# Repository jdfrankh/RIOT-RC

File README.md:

### RIOT-RC
This library contains hardware and software files for Robo RIOT's Rc controllers. These sets are meant to control 1lb, 3lb, and possibly 5lb robotics in a compact package, allowing any individual to easily create their own open-source battle bot electronics set.  

## Quickstart -- Preassembled Remote and Receiver

The RIOT RC has the following basic specs

# Receiver
| Parameter | Value |
|----------|----------|
| Supply Voltage  | 5V - 36V  |
| Idle Amperage Time  | .05A  |
| Default ESC Hookups | 2 |
| Default Servo Hookups | 2 |
| DC Drives | 2 |

# Remote 
| Parameter | Value |
|----------|----------|
| Operating Time | ~3 hours  |
| Radio Range  | ~40-60m  |
| Analog Joysticks | 2 |
| Buttons | 4 |

# Hookup

The pinout of the Receiver is the following:

Attach your receiver as according to the diagram:

# Basic Operation

The staring operation of the remote goes as such.

1. Start your remote
2. Select your desired reciever by username
3. Control your reciever

The controls for selecting your receiver go as such:

The OLED screen will display all **Powered** receivers automatically with their assigned name. Select one to automatically connect it. 

The controls for the remote after the reciver go as such: 

Keep in mind that there is a **Software** based arming mechanism for the BLDC motor. The receiver will not activate it unless the arming command is first sent. It may take about 5 seconds to arm your receiver. **Please be cautious when actiavate the BLDC, as it's speed rating may be enough to harm.**

The brushed motors are programmed to act as a drive, moving according to a two wheeled battlebot. Although the supply voltage is attached to the motor drive, the original code is deisgned around a 6V N20, and thus creates a PWM signal to prevent users from frying the motor. To change this. Please refer to the **Change code** section for more information.

## Simple edits - Uploading Sketches

Many values as of right now are hard-coded into the remote or receiver to change, and most of those changes can be altered by re-flashing them. The software was created in PlatoformIO, and integrated IDE into VSCode for microcontrollers. Many resources are avaliable for you to download and operate the software.

Once PlatformIO has been downloaded, clone the repository and naviage to /RIOT-RC/PlatformIO Imports/ and select the platoformIO directory. 

**Caution**: The receiver is attached to the battery voltage. **FOR THE RECEIVER DO NOT ATTACH A USB WHILE A LIPO BATTERY IS ATTACHED. YOU WILL FRY YOUR USB PORT AND YOUR COMPUTER**

Most easily accessible commands will be placed at the top of main.cpp for ease of access. Alterations from the basic control scheme will be implemented later. 

# Battery Charging

The Remote has a one cell battery charger. Simply attach the charger to your USB to recharge it.

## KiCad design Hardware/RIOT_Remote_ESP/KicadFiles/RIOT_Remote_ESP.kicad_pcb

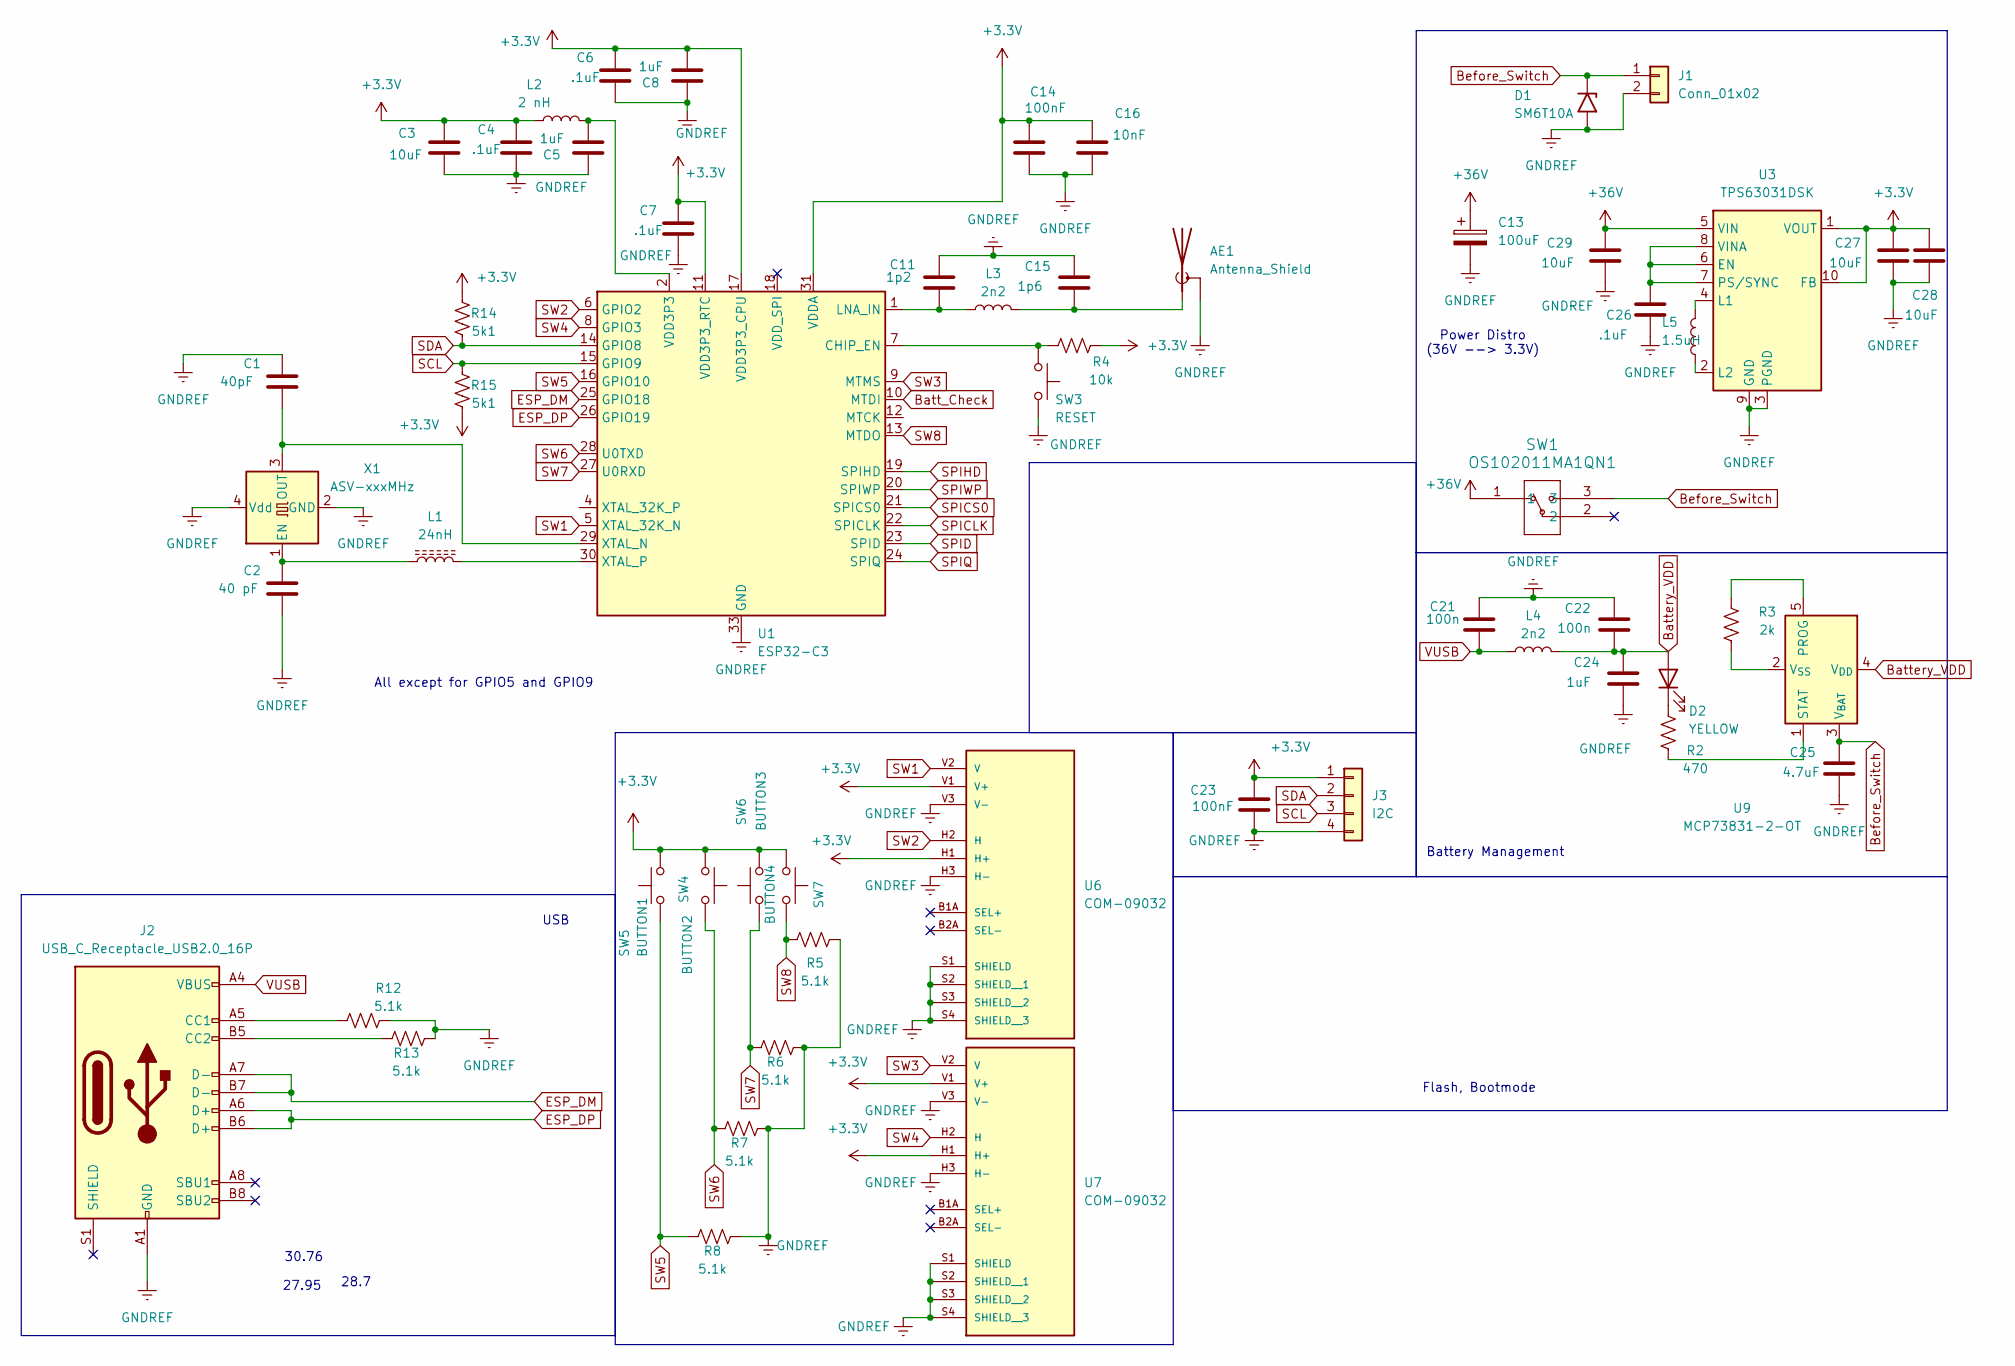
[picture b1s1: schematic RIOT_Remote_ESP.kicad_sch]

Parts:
AE1: Antenna_Shield; U.FL_Molex_MCRF_73412-0110_Vertical
C1: 40pF; C_0402_1005Metric_Pad0.74x0.62mm_HandSolder
C2: 40 pF; C_0402_1005Metric_Pad0.74x0.62mm_HandSolder
C3: 10uF; C_1206_3216Metric_Pad1.33x1.80mm_HandSolder
C4, C6, C7, C26: .1uF; C_0402_1005Metric_Pad0.74x0.62mm_HandSolder
C5, C8, C24: 1uF; C_0402_1005Metric_Pad0.74x0.62mm_HandSolder
C11: 1p2; C_0402_1005Metric_Pad0.74x0.62mm_HandSolder
C13: 100uF; CP_Elec_4x5.4
C14, C23: 100nF; C_0402_1005Metric_Pad0.74x0.62mm_HandSolder
C15: 1p6; C_0402_1005Metric_Pad0.74x0.62mm_HandSolder
C16: 10nF; C_0402_1005Metric_Pad0.74x0.62mm_HandSolder
C21, C22: 100n; C_0402_1005Metric_Pad0.74x0.62mm_HandSolder
C25: 4.7uF; C_0402_1005Metric_Pad0.74x0.62mm_HandSolder
C27, C28, C29: 10uF; C_0603_1608Metric_Pad1.08x0.95mm_HandSolder
D1: SM6T10A; D_SMB
D2: YELLOW; LED_1206_3216Metric_Pad1.42x1.75mm_HandSolder
J1: Conn_01x02; PinSocket_1x02_P2.54mm_Vertical
J2: USB_C_Receptacle_USB2.0_16P; USB_C_Receptacle_GCT_USB4085
J3: I2C; PinHeader_1x04_P2.54mm_Vertical
L1: 24nH; L_0603_1608Metric_Pad1.05x0.95mm_HandSolder
L2: 2 nH; L_0603_1608Metric_Pad1.05x0.95mm_HandSolder
L3, L4: 2n2; L_0603_1608Metric_Pad1.05x0.95mm_HandSolder
L5: 1.5uH; L_Coilcraft_LPS3010
R2: 470; R_0402_1005Metric_Pad0.72x0.64mm_HandSolder
R3: 2k; R_0402_1005Metric_Pad0.72x0.64mm_HandSolder
R4: 10k; R_0402_1005Metric_Pad0.72x0.64mm_HandSolder
R5, R6, R7, R8, R12, R13: 5.1k; R_0402_1005Metric_Pad0.72x0.64mm_HandSolder
R14, R15: 5k1; R_0402_1005Metric_Pad0.72x0.64mm_HandSolder
SW1: OS102011MA1QN1; OS102011MA1QN1_CNK
SW3: RESET; SW_PUSH_6mm_H4.3mm
SW4: BUTTON2; SW_Tactile_SPST_Angled_PTS645Vx58-2LFS
SW5: BUTTON1; SW_PUSH_6mm_H4.3mm
SW6: BUTTON3; SW_PUSH_6mm_H4.3mm
SW7: BUTTON4; SW_Tactile_SPST_Angled_PTS645Vx58-2LFS
U1: ESP32-C3; QFN-32-1EP_5x5mm_P0.5mm_EP3.7x3.7mm
U3: TPS63031DSK; WSON-10-1EP_2.5x2.5mm_P0.5mm_EP1.2x2mm
U6, U7: COM-09032; XDCR_COM-09032; PARTREV N/A
U9: MCP73831-2-OT; SOT-23-5
X1: ASV-xxxMHz; Oscillator_SMD_Abracon_ASE-4Pin_3.2x2.5mm_HandSoldering

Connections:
+3.3V: C3.1, C4.1, C6.1, C7.1, C8.2, C14.1, C16.1, C23.1, C27.1, C28.1, J3.1, L2.1, R4.2, R14.2, R15.1, SW4.1, SW5.2, SW6.2, SW7.1, U1.11 (VDD3P3_RTC), U1.17 (VDD3P3_CPU), U1.31 (VDDA), U1.32 (VDDA), U3.1 (VOUT), U3.10 (FB), U6.H1 (H+), U6.V1 (V+), U7.H1 (H+), U7.V1 (V+)
+36V: C13.1, C29.1, SW1.1, U3.5 (VIN); also elsewhere on the board
Batt_Check: U1.10 (MTDI)
Battery_VDD: C22.2, C24.1, D2.2 (A), L4.2, U9.4 (V_{DD})
Before_Switch: C25.1, D1.1 (A1), J1.1, SW1.3, U9.3 (V_{BAT}); also elsewhere on the board
ESP_DM: J2.A7 (D-), J2.B7 (D-), U1.25 (GPIO18)
ESP_DP: J2.A6 (D+), J2.B6 (D+), U1.26 (GPIO19)
GNDREF: AE1.2 (Shield), C1.1, C2.2, C3.2, C4.2, C5.1, C6.2, C7.2, C8.1, C11.1, C13.2, C14.2, C15.1, C16.2, C21.1, C22.1, C23.2, C24.2, C25.2, C26.2, C27.2, C28.2, C29.2, D1.2 (A2), J1.2, J2.A1 (GND), J2.A12 (GND), J2.B1 (GND), J2.B12 (GND), J3.4, R5.2, R6.2, R7.2, R8.2, R12.2, R13.2, SW3.2, U1.33 (GND), U3.3 (PGND), U3.9 (GND), U3.11 (PGND), U6.H3 (H-), U6.S1 (SHIELD), U6.S2 (SHIELD__1), U6.S3 (SHIELD__2), U6.S4 (SHIELD__3), U6.V3 (V-), U7.H3 (H-), U7.S1 (SHIELD), U7.S2 (SHIELD__1), U7.S3 (SHIELD__2), U7.S4 (SHIELD__3), U7.V3 (V-), X1.2 (GND), X1.4 (Vdd); also elsewhere on the board
unnamed: AE1.1 (A), C15.2, L3.2
unnamed: C5.2, L2.2, U1.2 (VDD3P3), U1.3 (VDD3P3)
unnamed: D2.1 (K), R2.2
unnamed: J2.A5 (CC1), R12.1
unnamed: J2.B5 (CC2), R13.1
unnamed: R4.1, SW3.1, U1.7 (CHIP_EN)
unnamed: C11.2, L3.1, U1.1 (LNA_IN)
unnamed: C1.2, U1.29 (XTAL_N), X1.3 (OUT)
unnamed: L1.2, U1.30 (XTAL_P)
unnamed: C26.1, U3.6 (EN), U3.7 (PS/SYNC), U3.8 (VINA)
unnamed: L5.2, U3.4 (L1)
unnamed: L5.1, U3.2 (L2)
unnamed: R3.2, U9.5 (PROG)
unnamed: R2.1, U9.1 (STAT)
unnamed: R3.1, U9.2 (V_{SS})
unnamed: C2.1, L1.1, X1.1 (EN)
SCL: J3.3, R15.2, U1.15 (GPIO9)
SDA: J3.2, R14.1, U1.14 (GPIO8)
SPICLK: U1.22 (SPICLK)
SPICS0: U1.21 (SPICS0)
SPID: U1.23 (SPID)
SPIHD: U1.19 (SPIHD)
SPIQ: U1.24 (SPIQ)
SPIWP: U1.20 (SPIWP)
SW1: U1.5 (XTAL_32K_N), U6.V2 (V)
SW2: U1.6 (GPIO2), U6.H2 (H)
SW3: U1.9 (MTMS), U7.V2 (V)
SW4: U1.8 (GPIO3), U7.H2 (H)
SW5: R8.1, SW5.1, U1.16 (GPIO10)
SW6: R7.1, SW4.2, U1.28 (U0TXD)
SW7: R6.1, SW6.1, U1.27 (U0RXD)
SW8: R5.1, SW7.2, U1.13 (MTDO)
VUSB: C21.2, J2.A4 (VBUS), J2.A9 (VBUS), J2.B4 (VBUS), J2.B9 (VBUS), L4.1

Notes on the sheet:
28.7
Battery Management
Power Distro (36V --> 3.3V)
Flash, Bootmode
27.95
All except for GPIO5 and GPIO9
USB
30.76

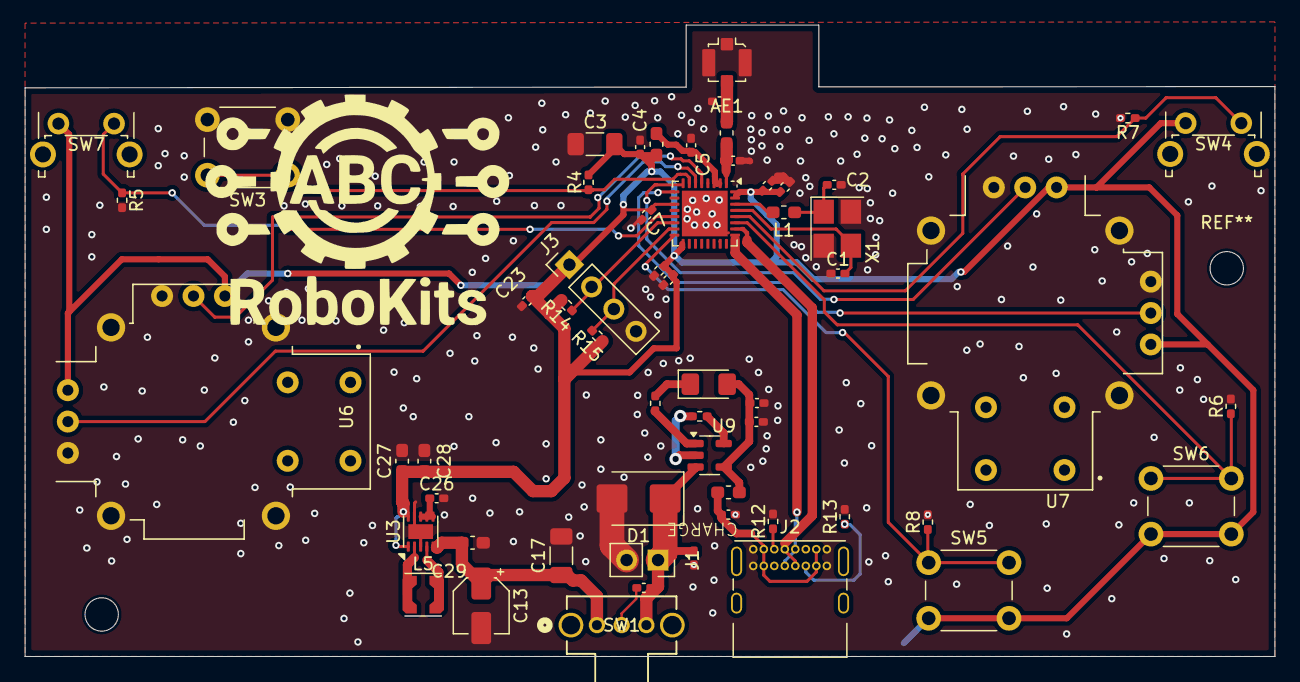
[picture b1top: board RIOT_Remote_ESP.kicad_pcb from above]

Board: 2 copper layers, 101.1 x 51.1 mm, 58 parts (0 on the bottom side), 34 nets.

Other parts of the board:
C17: 1 uF; C_1206_3216Metric_Pad1.33x1.80mm_HandSolder
C25#2: 4.7uF; C_0402_1005Metric_Pad0.74x0.62mm_HandSolder

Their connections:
+36V: C17.1; also elsewhere on the board
Before_Switch: C25#2.1; also elsewhere on the board
GNDREF: C17.2, C25#2.2; also elsewhere on the board

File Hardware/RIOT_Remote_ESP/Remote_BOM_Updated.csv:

Value,Reference,Footprint,Digikey Link to Item,Qty
MCP73831-2-OT,U9,Package_TO_SOT_SMD:SOT-23-5,https://www.digikey.com/en/products/filter/battery-chargers/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,1
ASV-40MHz,X1,Oscillator:Oscillator_SMD_Abracon_ASE-4Pin_3.2x2.5mm_HandSoldering,https://www.digikey.com/en/products/detail/kyocera-avx/CX322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,1
TPS63031DSK,U3,Package_SON:WSON-10-1EP_2.5x2.5mm_P0.5mm_EP1.2x2mm,https://www.digikey.com/en/products/detail/texas-instruments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,1
ESP32-C3FH,U1,Package_DFN_QFN:QFN-32-1EP_5x5mm_P0.5mm_EP3.7x3.7mm,https://www.digikey.com/en/products/detail/espressif-systems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,1
SM6T10A,D1,Diode_SMD:D_SMB,https://www.digikey.com/en/products/detail/stmicroelectronic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,1
USB_C_Receptacle_USB2.0_16P,J2,Connector_USB:USB_C_Receptacle_GCT_USB4085,https://www.digikey.com/en/products/detail/gct/USB4085-GF-A/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,1
Antenna_Shield,AE1,Connector_Coaxial:U.FL_Molex_MCRF_73412-0110_Vertical,https://www.digikey.com/en/products/detail/hirose-electric-c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,1
12pF,"C1,C2",Capacitor_SMD:C_0402_1005Metric_Pad0.74x0.62mm_HandSolder,,2
10uF,"C3,C27,C28,C29","Capacitor_SMD:C_0603_1608Metric_Pad1.08x0.95mm_HandSolder,Capacitor_SMD:C_1206_3216Metric_Pad1.33x1.80mm_HandSolder",,4
1uF,"C5,C8,C24",Capacitor_SMD:C_0402_1005Metric_Pad0.74x0.62mm_HandSolder,,3
1p2,C11,Capacitor_SMD:C_0402_1005Metric_Pad0.74x0.62mm_HandSolder,,1
100uF,C13,Capacitor_SMD:CP_Elec_4x5.4,,1
100nF,"C14,C23,C21,C22,C4,C6,C7,C26",Capacitor_SMD:C_0402_1005Metric_Pad0.74x0.62mm_HandSolder,,8
1p6,C15,Capacitor_SMD:C_0402_1005Metric_Pad0.74x0.62mm_HandSolder,,1
10nF,C16,Capacitor_SMD:C_0402_1005Metric_Pad0.74x0.62mm_HandSolder,,1
4.7uF,C25,Capacitor_SMD:C_0402_1005Metric_Pad0.74x0.62mm_HandSolder,,1
YELLOW,D2,LED_SMD:LED_1206_3216Metric_Pad1.42x1.75mm_HandSolder,,1
24nH,L1,Inductor_SMD:L_0603_1608Metric_Pad1.05x0.95mm_HandSolder,,1
2 nH,L2,Inductor_SMD:L_0603_1608Metric_Pad1.05x0.95mm_HandSolder,,1
2n2,"L3,L4",Inductor_SMD:L_0603_1608Metric_Pad1.05x0.95mm_HandSolder,,2
1.5uH,L5,Inductor_SMD:L_Coilcraft_LPS3010,,1
470,R2,Resistor_SMD:R_0402_1005Metric_Pad0.72x0.64mm_HandSolder,,1
2k,R3,Resistor_SMD:R_0402_1005Metric_Pad0.72x0.64mm_HandSolder,,1
10k,R4,Resistor_SMD:R_0402_1005Metric_Pad0.72x0.64mm_HandSolder,,1
5.1k,"R14,R15,R5,R6,R7,R8,R12,R13",Resistor_SMD:R_0402_1005Metric_Pad0.72x0.64mm_HandSolder,,8

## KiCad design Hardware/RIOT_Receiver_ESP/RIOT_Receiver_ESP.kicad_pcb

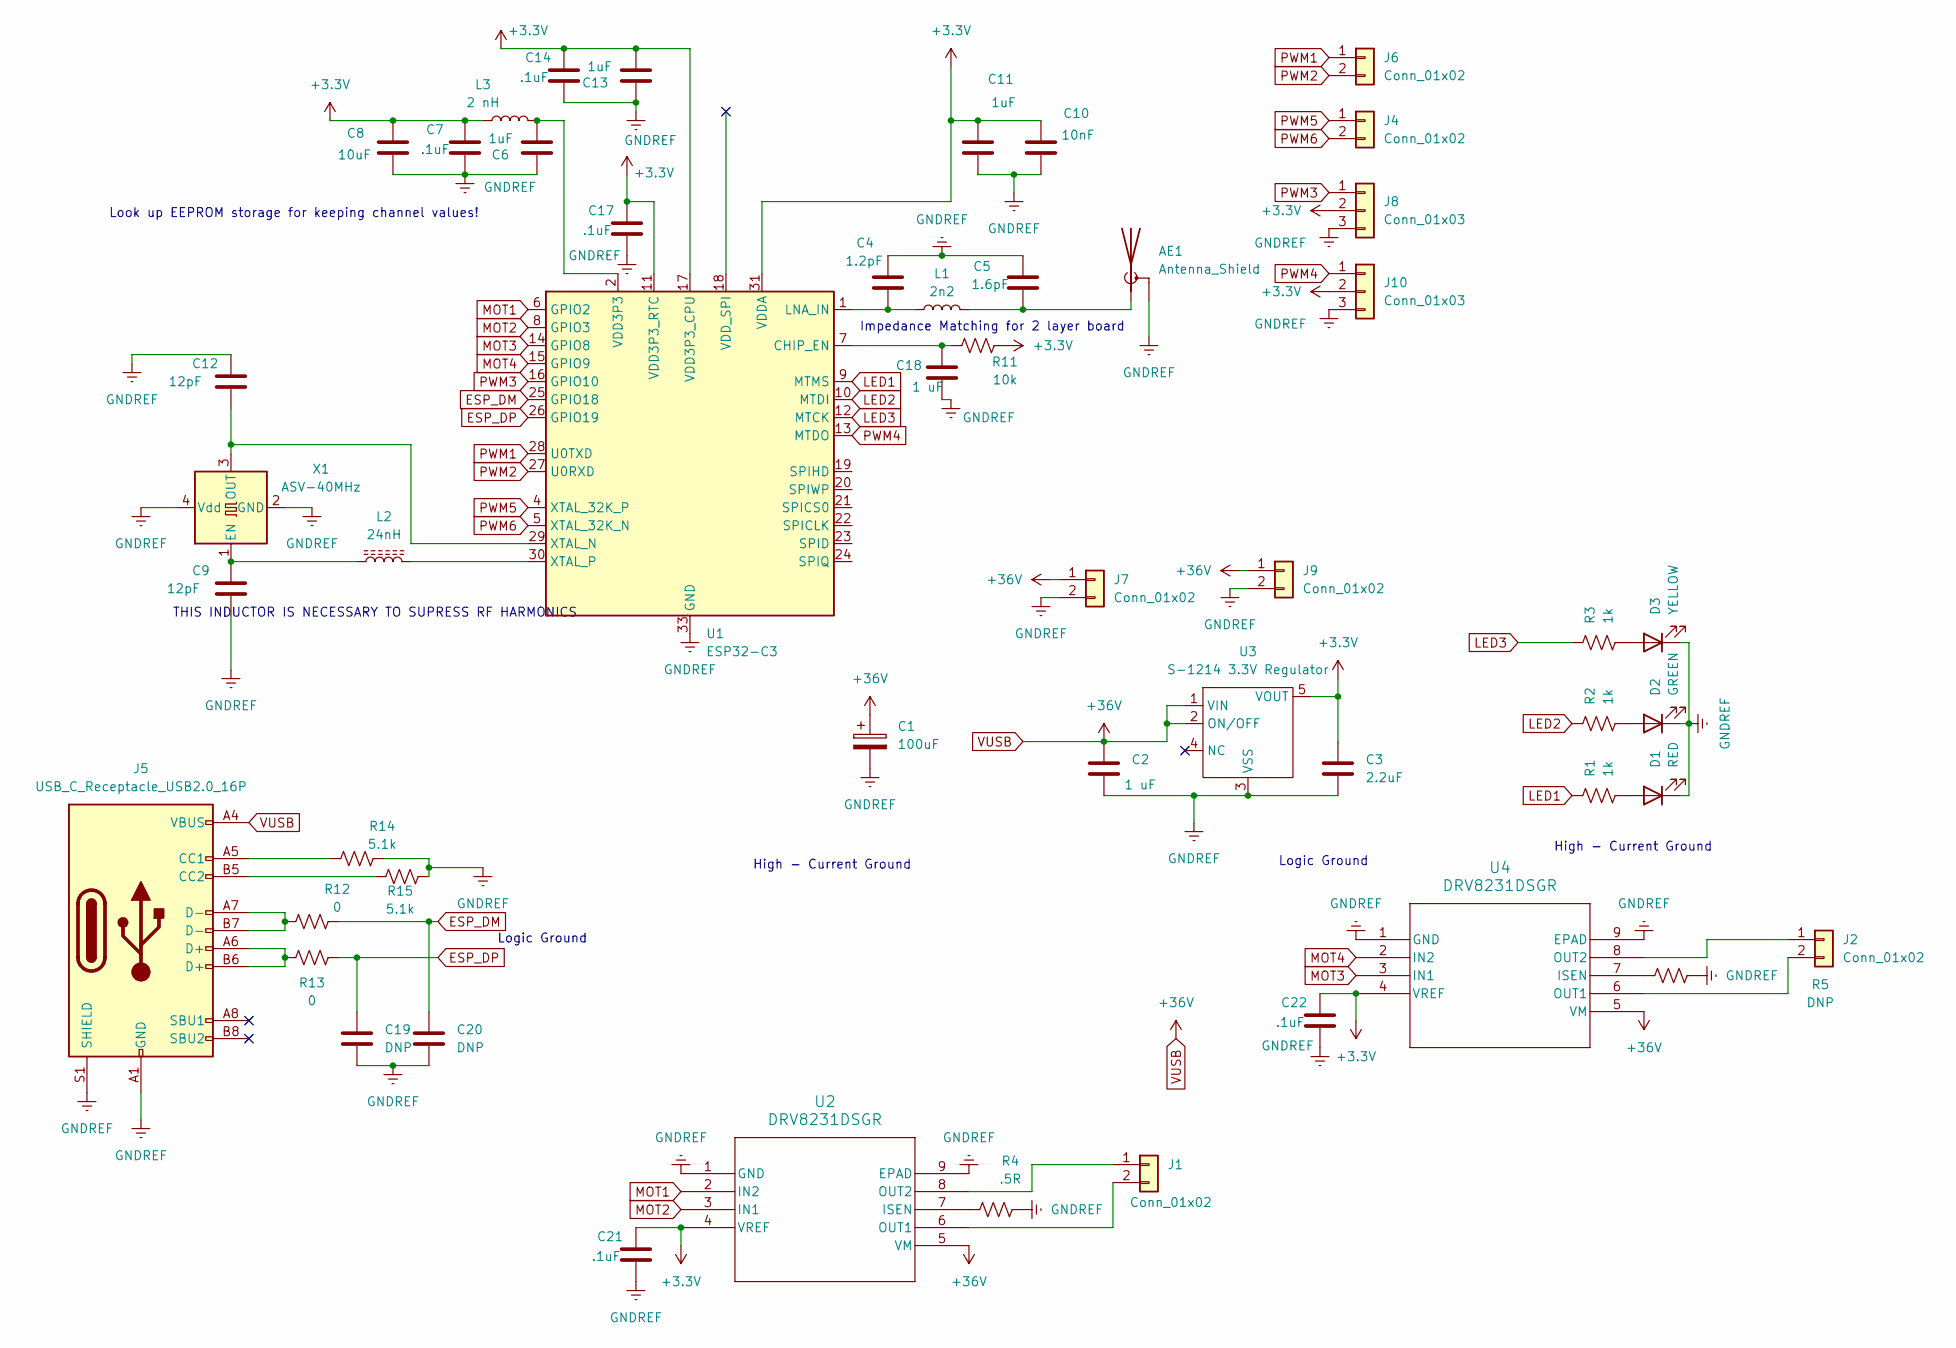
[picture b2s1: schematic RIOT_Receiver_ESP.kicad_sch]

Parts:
AE1: Antenna_Shield
C1: 100uF; C_Elec_8x10.2
C2, C18: 1 uF; C_0402_1005Metric_Pad0.74x0.62mm_HandSolder
C3: 2.2uF; C_0603_1608Metric_Pad1.08x0.95mm_HandSolder
C4: 1.2pF; C_0402_1005Metric_Pad0.74x0.62mm_HandSolder
C5: 1.6pF; C_0402_1005Metric_Pad0.74x0.62mm_HandSolder
C6, C11, C13: 1uF; C_0402_1005Metric_Pad0.74x0.62mm_HandSolder
C7, C14, C17, C21, C22: .1uF; C_0402_1005Metric_Pad0.74x0.62mm_HandSolder
C8: 10uF; C_0402_1005Metric_Pad0.74x0.62mm_HandSolder
C9, C12: 12pF; C_0402_1005Metric_Pad0.74x0.62mm_HandSolder
C10: 10nF; C_0402_1005Metric_Pad0.74x0.62mm_HandSolder
C19, C20: DNP; C_0402_1005Metric_Pad0.74x0.62mm_HandSolder
D1: RED; LED_1206_3216Metric_Pad1.42x1.75mm_HandSolder
D2: GREEN; LED_1206_3216Metric_Pad1.42x1.75mm_HandSolder
D3: YELLOW; LED_1206_3216Metric_Pad1.42x1.75mm_HandSolder
J1, J2, J4, J6, J7, J9: Conn_01x02; PinHeader_1x02_P2.54mm_Vertical
J5: USB_C_Receptacle_USB2.0_16P; USB_C_Receptacle_GCT_USB4085
J8, J10: Conn_01x03; PinHeader_1x03_P2.54mm_Vertical
L1: 2n2; L_0603_1608Metric_Pad1.05x0.95mm_HandSolder
L2: 24nH; L_0603_1608Metric_Pad1.05x0.95mm_HandSolder
L3: 2 nH; L_0603_1608Metric_Pad1.05x0.95mm_HandSolder
R1, R2, R3: 1k; R_0402_1005Metric_Pad0.72x0.64mm_HandSolder
R4: .5R; L_1206_3216Metric_Pad1.22x1.90mm_HandSolder
R5: DNP; L_1206_3216Metric_Pad1.22x1.90mm_HandSolder
R11: 10k; R_0402_1005Metric_Pad0.72x0.64mm_HandSolder
R12, R13: 0; R_0402_1005Metric_Pad0.72x0.64mm_HandSolder
R14, R15: 5.1k; R_0402_1005Metric_Pad0.72x0.64mm_HandSolder
U1: ESP32-C3; QFN-32-1EP_5x5mm_P0.5mm_EP3.7x3.7mm
U2, U4: DRV8231DSGR; WSON8_DRV8231_TEX
U3: S-1214 3.3V Regulator; TO-252-5_TabPin3
X1: ASV-40MHz; Oscillator_SMD_Abracon_ASE-4Pin_3.2x2.5mm

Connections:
+3.3V: C3.1, C7.1, C8.1, C10.1, C11.1, C13.2, C14.1, C17.1, C21.1, C22.1, J8.2, J10.2, L3.1, R11.2, U1.11 (VDD3P3_RTC), U1.17 (VDD3P3_CPU), U1.31 (VDDA), U1.32 (VDDA), U2.4 (VREF), U3.5 (VOUT), U4.4 (VREF)
ESP_DM: C20.1, R12.2, U1.25 (GPIO18)
ESP_DP: C19.1, R13.1, U1.26 (GPIO19)
GNDREF: AE1.2 (Shield), C1.2, C2.2, C3.2, C4.1, C5.1, C6.1, C7.2, C8.2, C9.2, C10.2, C11.2, C12.1, C13.1, C14.2, C17.2, C18.2, C19.2, C20.2, C21.2, C22.2, D1.1 (K), D2.1 (K), D3.1 (K), J5.A1 (GND), J5.A12 (GND), J5.B1 (GND), J5.B12 (GND), J5.S1 (SHIELD), J7.2, J8.3, J9.2, J10.3, R4.2, R5.2, R14.2, R15.2, U1.33 (GND), U2.1 (GND), U2.9 (EPAD), U3.3 (VSS), U4.1 (GND), U4.9 (EPAD), X1.2 (GND), X1.4 (Vdd)
LED1: R1.1, U1.9 (MTMS)
LED2: R2.1, U1.10 (MTDI)
LED3: R3.1, U1.12 (MTCK)
MOT1: U1.6 (GPIO2), U2.2 (IN2)
MOT2: U1.8 (GPIO3), U2.3 (IN1)
MOT3: U1.14 (GPIO8), U4.3 (IN1)
MOT4: U1.15 (GPIO9), U4.2 (IN2)
unnamed: AE1.1 (A), C5.2, L1.2
unnamed: C6.2, L3.2, U1.2 (VDD3P3), U1.3 (VDD3P3)
unnamed: D1.2 (A), R1.2
unnamed: D2.2 (A), R2.2
unnamed: D3.2 (A), R3.2
unnamed: J1.1, U2.8 (OUT2)
unnamed: J1.2, U2.6 (OUT1)
unnamed: J2.1, U4.8 (OUT2)
unnamed: J2.2, U4.6 (OUT1)
unnamed: J5.A5 (CC1), R14.1
unnamed: J5.B5 (CC2), R15.1
unnamed: J5.A6 (D+), J5.B6 (D+), R13.2
unnamed: J5.A7 (D-), J5.B7 (D-), R12.1
unnamed: C18.1, R11.1, U1.7 (CHIP_EN)
unnamed: C4.2, L1.1, U1.1 (LNA_IN)
unnamed: C12.2, U1.29 (XTAL_N), X1.3 (OUT)
unnamed: L2.2, U1.30 (XTAL_P)
unnamed: R4.1, U2.7 (ISEN)
unnamed: R5.1, U4.7 (ISEN)
unnamed: C9.1, L2.1, X1.1 (EN)
PWM1: J6.1, U1.28 (U0TXD)
PWM2: J6.2, U1.27 (U0RXD)
PWM3: J8.1, U1.16 (GPIO10)
PWM4: J10.1, U1.13 (MTDO)
PWM5: J4.1, U1.4 (XTAL_32K_P)
PWM6: J4.2, U1.5 (XTAL_32K_N)
VUSB: C1.1, C2.1, J5.A4 (VBUS), J5.A9 (VBUS), J5.B4 (VBUS), J5.B9 (VBUS), J7.1, J9.1, U2.5 (VM), U3.1 (VIN), U3.2 (ON/OFF), U4.5 (VM)

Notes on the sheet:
THIS INDUCTOR IS NECESSARY TO SUPRESS RF HARMONICS
Logic Ground
High - Current Ground
Look up EEPROM storage for keeping channel values!
Impedance Matching for 2 layer board

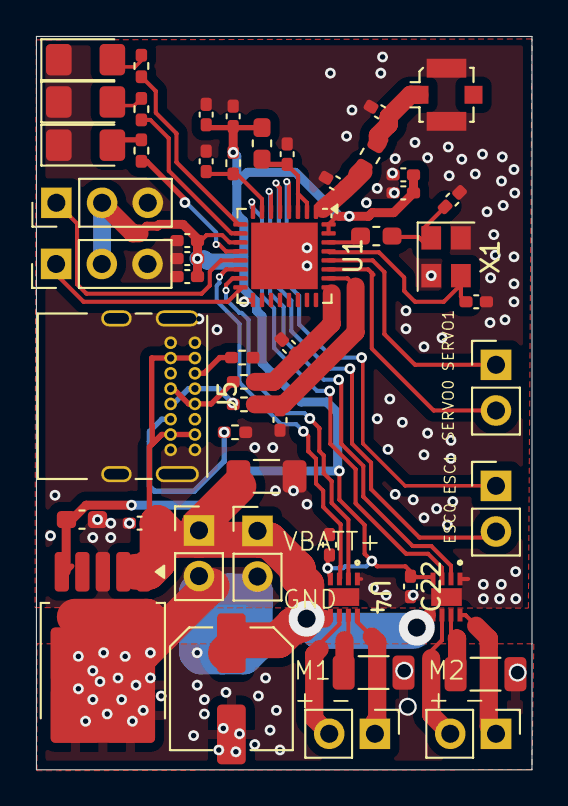
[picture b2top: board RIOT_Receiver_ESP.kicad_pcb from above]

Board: 2 copper layers, 27.5 x 40.7 mm, 49 parts (0 on the bottom side), 38 nets.

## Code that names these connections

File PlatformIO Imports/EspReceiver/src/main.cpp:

#include <Arduino.h>
#include <WiFi.h>
#include "EspNowEZ.h"
#include <esp_now.h>
#include <esp_system.h>
#include "esp_wifi.h"
#include <ESP32Servo.h>
#include <vector>
#include "ESC.h" // RC_ESP library installed by Library Manager

const uint8_t broadcastAddress[] = {0xFF, 0xFF, 0xFF, 0xFF, 0xFF, 0xFF};
int timeout = 0;
bool receivedRemoteSignal = false; 

#define Mot1 2
#define Mot2 3

#define Mot3 8
#define Mot4 9


#define ESC1 0
#define ESC2 1

//Servo library defaults from 20 to 180
#define ESCSMINDISTANCE 1000
#define ESCMAXDISTANCE 1900

#define SERVO1 10
#define SERVO2 7

#define SERVOIDLEANGLE 0
#define SERVOARMANGLE 90
#define SERVOATTACKANGLE 180

#define PWM1 20
#define PWM2 21

#define LED1 4
#define LED2 5
#define LED3 6


Servo FirstESC;
float escSpeed1 = 0;
ESC SecondESC(ESC2, 1000, 2000, 1000); 
uint16_t escSpeed2 = 0;
bool ESCArm[2] = {false, false};





//struct __attribute__((packed)) Message{
  const char id[20] = "Spenc";
//};



struct __attribute__((packed)) sendData{
    uint8_t macHandshake[6];
    uint8_t Direction[2]; // 0,1,2,3 FWD, BWD, Left, Right

    uint8_t DcMax[2] = {255,255};
    uint8_t DcMin[2] = {0,0};
    uint8_t dcMagnitude[2] = {0,0}; //Should be between 0 and 100
    bool objectArm[6]; // For escs, arm them, for servos, set to zero degrees? or fixable value
    bool objectRun[6]; 
    float escSpeed = .25; 

    bool connectCheck = false;
};

Container message;
uint8_t macAddress[6];
//Message msg;
sendData sD;
bool waitingForResponse(){

 

  //message.store(msg); 
  //message.printBytes();
  int result = esp_now_send(broadcastAddress, (uint8_t*) &id, sizeof(id) );
  //int result = ESPNow.broadcastMessage(message);
  result == ESP_OK ? digitalWrite(LED1, !digitalRead(LED1)) : digitalWrite(LED1, LOW);

  result == ESP_OK ? Serial.println("Sent successfully"): Serial.printf("Print failure %02x", ESP_OK);


  delay(250); // Send every 2 seconds


  return(true);

}

// Optional: callback for send status
//void onSend(const uint8_t *mac_addr, esp_now_send_status_t status) {

//}

void onReceive(const esp_now_recv_info *mac_info, const uint8_t *incomingData, int len) {
  const uint8_t *recv_info = mac_info->src_addr;
  
  if (len == sizeof(sendData)) {
    Serial.println("Data received from remote!"); 
    memcpy(&sD, incomingData, sizeof(sendData));

    //Serial.printf("%02x ,%02x,%02x,%20x: ", sD.Direction[0], sD.Direction[1], sD.objectRun[0], sD.objectArm[0]);
  //  for(size_t i= 0; i < len; i++){
  //    Serial.printf("%02X,", incomingData[i]);
  //  }
  //  Serial.printf("Length: %d", len);
  //  Serial.printf(": %d", sD.Direction[0]);
  //  Serial.println();

  //Serial.printf("Arm 0: %d, Arm 1: %d, Interact 0: %d, Interact 1: %d" , sD.objectArm[0],sD.objectArm[1], sD.objectRun[0], sD.objectRun[1] );
  //Serial.println();

    if (!esp_now_is_peer_exist(sD.macHandshake)) {
    Serial.println("Adding peer");
    ESPNow.add_peer(sD.macHandshake);
    }
    
    digitalWrite(LED2, HIGH);
    timeout = 1000;



    if(sD.macHandshake[5] == macAddress[5] && sD.macHandshake[4] == macAddress[4] && sD.macHandshake[3] == macAddress[3] ){
      digitalWrite(LED3, HIGH);
    }

  } else {
    Serial.print("Unexpected message length: ");
    Serial.println(len);
  }


}




void mapFunction(){
//  Serial.println("Mapping");

  if(sD.objectArm[0]){
    digitalWrite(LED3, HIGH);
    Serial.println("Arming");
    FirstESC.detach();

    //digitalWrite(ESC2, LOW);
    delay(100);
    FirstESC.attach(ESC2); // Send the Arm command to ESC
    FirstESC.writeMicroseconds(ESCSMINDISTANCE);


    ESCArm[0] = true;
    Serial.println("Done Arming");
  }

  if(ESCArm[0] && sD.objectRun[0]){
    
    if(escSpeed1 < (ESCMAXDISTANCE - ESCSMINDISTANCE)){ // Should be 7000
      escSpeed1+= sD.escSpeed;
    }

    FirstESC.writeMicroseconds(ESCSMINDISTANCE + int(escSpeed1) );
    digitalWrite(LED3, HIGH);
  }
  else if(!ESCArm[0]){
    //do nothing
  }
  else{
    digitalWrite(LED3, LOW);
    Serial.println("Stopping");
    if(escSpeed1 > 0){
      escSpeed1-=sD.escSpeed; 
    }
    FirstESC.writeMicroseconds(ESCSMINDISTANCE+ escSpeed1);
  }

  //Serial.printf("Max: %d : %d", sD.DcMax[0], sD.DcMax[1]);
  //Serial.println();

  //Serial.printf("Min: %d : %d", sD.DcMin[0], sD.DcMin[1]);
  //Serial.println();

  switch(sD.Direction[0]){
    case 0: // Stop
      analogWrite(Mot1, sD.DcMin[0]);
      analogWrite(Mot2, sD.DcMin[0]);
      analogWrite(Mot3, sD.DcMin[1]);
      analogWrite(Mot4, sD.DcMin[1]);
    break;
    case 1: // Forward
      analogWrite(Mot1, sD.DcMax[0]);
      analogWrite(Mot2, sD.DcMin[0]);
      analogWrite(Mot3, sD.DcMax[1]);
      analogWrite(Mot4, sD.DcMin[1]);
    break;
    case 2: // Backward
      analogWrite(Mot1, sD.DcMin[0]);
      analogWrite(Mot2, sD.DcMax[0]);
      analogWrite(Mot3, sD.DcMin[1]);
      analogWrite(Mot4, sD.DcMax[1]);
    break;
    case 3: // Left
      analogWrite(Mot1, sD.DcMin[0]);
      analogWrite(Mot2, sD.DcMax[0]);
      analogWrite(Mot3, sD.DcMax[1]);
      analogWrite(Mot4, sD.DcMin[1]);
    break;
    case 4: // Right
      analogWrite(Mot1, sD.DcMax[0]);
      digitalWrite(Mot2, sD.DcMin[0]);
      digitalWrite(Mot3, sD.DcMin[1]);
      analogWrite(Mot4, sD.DcMax[1]);
    break;
    default:
      analogWrite(Mot1, sD.DcMin[0]);
      analogWrite(Mot2, sD.DcMin[0]);
      analogWrite(Mot3, sD.DcMin[1]);
      analogWrite(Mot4, sD.DcMin[1]);
    break;

  };


}

void setup() {
//  delay(10000);
  Serial.begin(115200);
 // delay(1000);

  //delay(250);

  pinMode(Mot1, OUTPUT);
  pinMode(Mot2, OUTPUT);
  pinMode(Mot3, OUTPUT);
  pinMode(Mot4, OUTPUT);
  pinMode(LED1, OUTPUT);
  pinMode(LED2, OUTPUT);
  pinMode(LED3, OUTPUT);

//  pinMode(ESC1, OUTPUT);
 // pinMode(ESC2, OUTPUT);   

  digitalWrite(LED1,LOW);
  digitalWrite(LED2, LOW);
  digitalWrite(LED3, LOW);

  digitalWrite(Mot1, LOW);
  digitalWrite(Mot2, LOW);
  digitalWrite(Mot3, LOW);
  digitalWrite(Mot4, LOW);



  //ESP_ERROR_CHECK(esp_wifi_set_channel(chan,WIFI_SECOND_CHAN_NONE));

  WiFi.mode(WIFI_MODE_STA);
  WiFi.disconnect();
  ESPNow.init();
  WiFi.macAddress(macAddress); 
  WiFi.setTxPower(WIFI_POWER_19dBm);
  ESPNow.reg_recv_cb(onReceive);
  // Optional: set send callback if you want to track status
  //ESPNow.reg_send_cb(onSend);

  
  Serial.print("My MAC Address: ");
  Serial.printf("%02x:%02x:%02x:%02x:%02x:%02x", macAddress[0],macAddress[1],macAddress[2],macAddress[3],macAddress[4],macAddress[5]);


  // Initialize ESP-NOW
  if (esp_now_init() != ESP_OK) {
    Serial.println("Error initializing ESP-NOW");
    return;
  }
  ESPNow.add_peer((uint8_t*)broadcastAddress,0); 

}

void loop() {
  if(timeout > 0){
    digitalWrite(LED1, LOW);
    mapFunction();
    timeout--;
    delay(10);
  }
  else{
    digitalWrite(LED1,LOW);
    digitalWrite(LED2, LOW);
    waitingForResponse();
  }

}

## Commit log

2025-09-06 Add files via upload
    Hardware Upload
2025-10-22 Add files via upload
    Change to ESPNOW protocol
